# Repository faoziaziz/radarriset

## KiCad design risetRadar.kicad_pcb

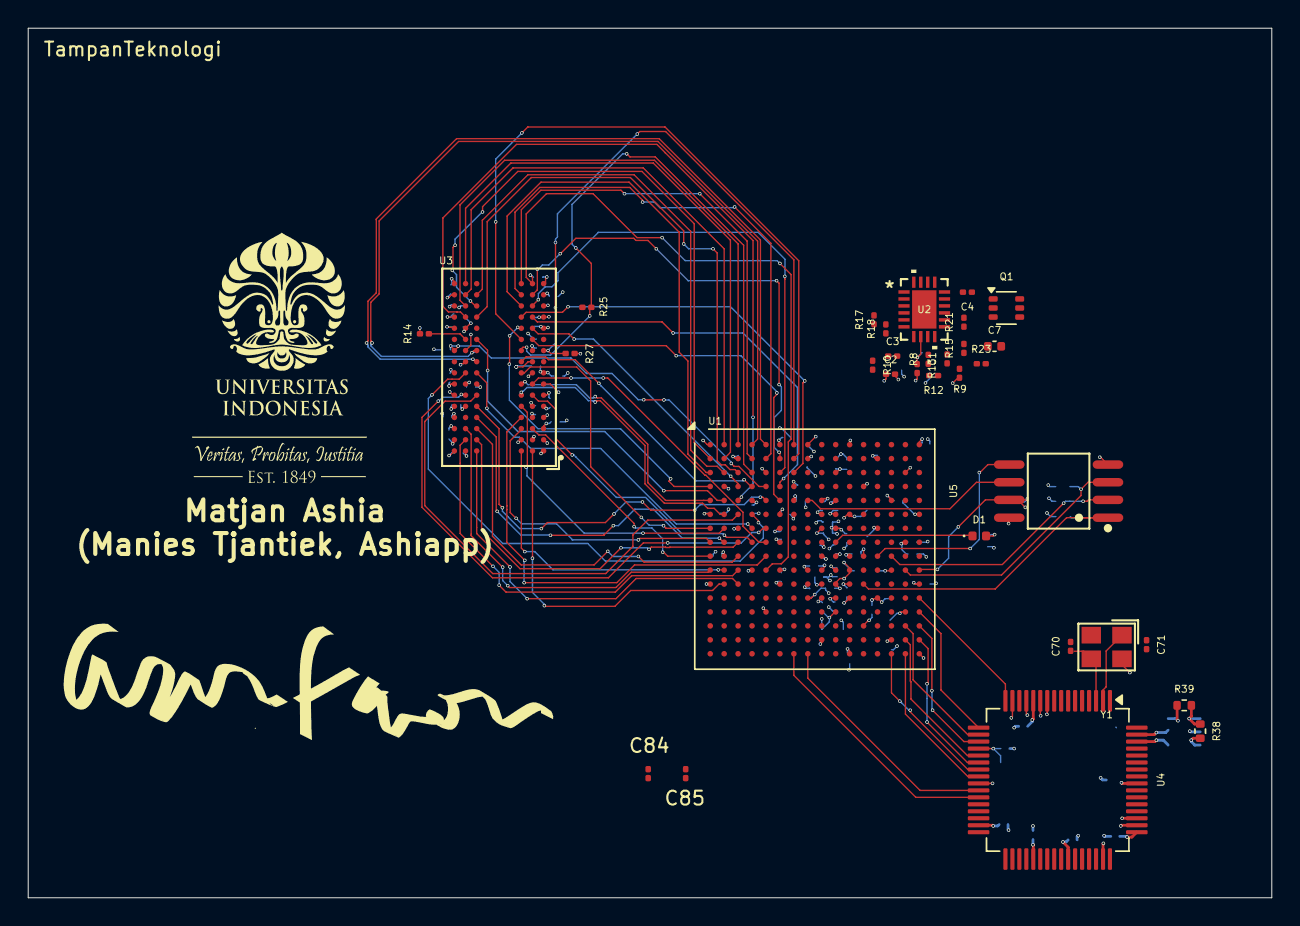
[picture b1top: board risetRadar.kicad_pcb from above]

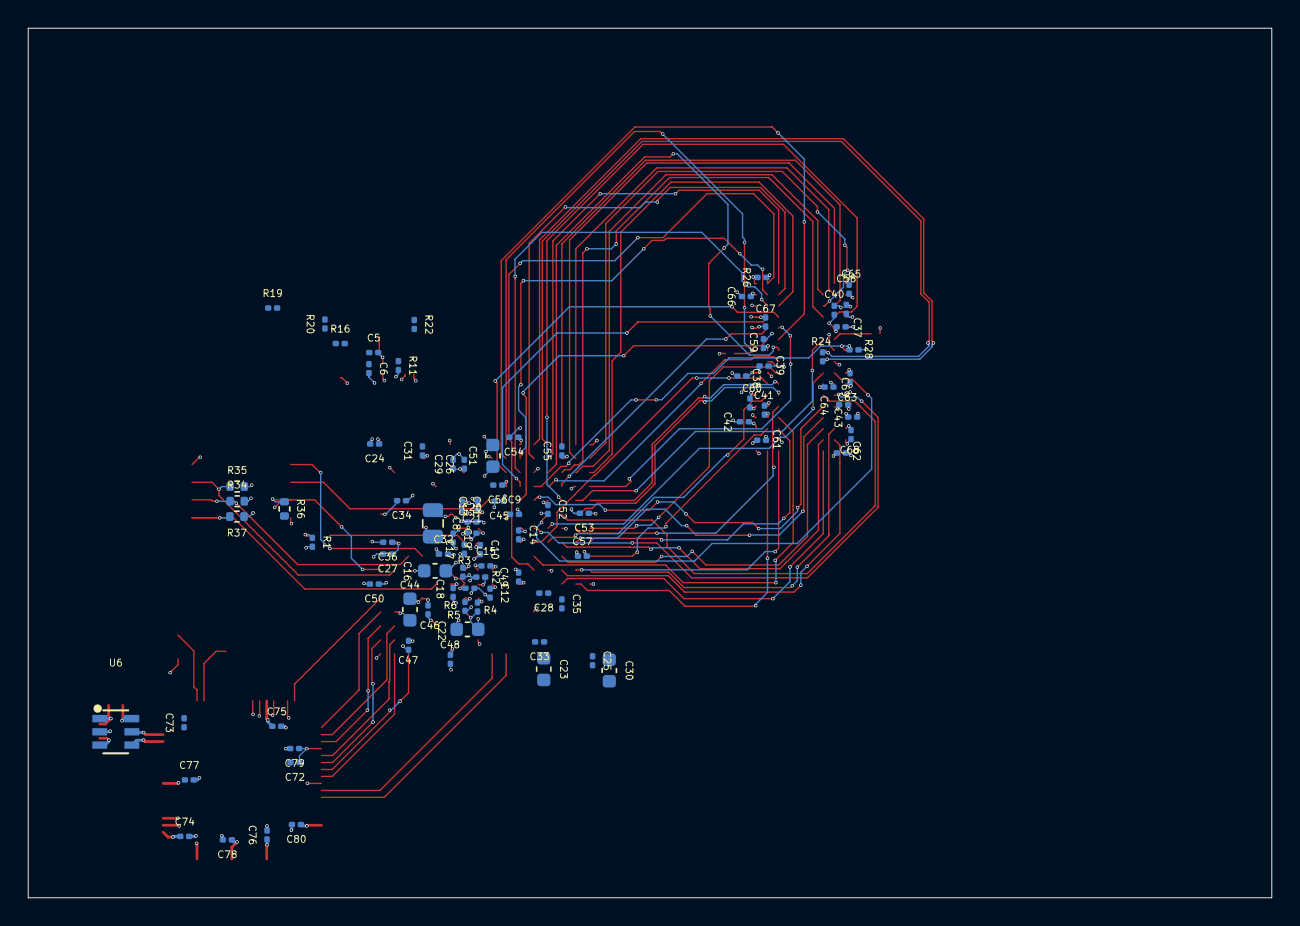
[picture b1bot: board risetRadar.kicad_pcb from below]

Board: 2 copper layers, 89.2 x 62.4 mm, 124 parts (92 on the bottom side), 96 nets.

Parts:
C1, C2, C3, C4, C5, C6: 20pF; C_0201_0603Metric
C7: 22uF; C_0402_1005Metric
C8: 100uF; C_0805_2012Metric
C9, C10, C14, C17, C18, C24, C25, C31, C32, C45, C46, C52, C53: 4.7uF; C_0201_0603Metric
C11, C12, C13, C15, C19, C20, C21, C26, C27, C28, C29, C33, C34, C35, C36, C47, C48, C49, C50, C54, C55, C56, C57, C84, C85: 0.47uF; C_0201_0603Metric
C16, C22, C23, C30, C44, C51: 47uF; C_0603_1608Metric
C37, C38, C39, C40, C41, C42, C43, C58, C59, C60, C61, C62, C63, C64, C65, C66, C67, C68, C69, C72, C73, C74, C75, C76, C77, C78, C79, C80: 0.1uF; C_0201_0603Metric
C70, C71: 8pF; C_0201_0603Metric
D1: LED; LED_0402_1005Metric
Q1: MBT3904DW1; SOT-363_SC-70-6
R1: 330R; R_0201_0603Metric
R2, R3, R26, R27, R28: 4.7K; R_0201_0603Metric
R4, R5, R6, R19: 1K; R_0201_0603Metric
R8, R10, R12: 180K; R_0201_0603Metric
R9, R11, R13: 57.6K; R_0201_0603Metric
R14: 240R; R_0201_0603Metric
R15: 3.48K; R_0201_0603Metric
R16: 10K; R_0201_0603Metric
R17, R20, R21, R22: 100K; R_0201_0603Metric
R18: 0; R_0201_0603Metric
R23: 680; R_0201_0603Metric
R24, R25: 100R; R_0201_0603Metric
R34, R37: 4.7K; R_0402_1005Metric
R35, R36: 1.8K; R_0402_1005Metric
R38: 2K; R_0402_1005Metric
R39: 10K; R_0402_1005Metric
U1: XC7A35T-FTG256; Xilinx_FTG256
U2: LTC3569EUDC; QFN-20_UDC_LIT
U3: MT41J128M16JT-125:KTR; FBGA-96_L14.0-W8.0-R16-C6-P0.80-TL
U4: FT2232HL; LQFP-64_10x10mm_P0.5mm
U5: MT25QL128ABA1ESE-MSITTR; SOP-8_L5.3-W5.3-P1.27-LS8.0-BL
U6: 93LC46BT-I/OT; SOT-23-6_L2.9-W1.6-P0.95-LS2.8-TL
Y1: Crystal_GND24; CRYSTAL-SMD_4P-L3.2-W2.5-BL

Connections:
/FPGA/FGPA_config/DONE: D1.1 (K), U1.H10 (DONE_0)
/FPGA/FGPA_config/INIT_B: R3.1, U1.K10 (INIT_B_0)
/FPGA/FGPA_config/M0: R4.1, U1.M9 (M0_0)
/FPGA/FGPA_config/M1: R5.1, U1.M10 (M1_0)
/FPGA/FGPA_config/M2: R6.1, U1.M11 (M2_0)
/FPGA/FGPA_config/PROG_B: R2.1, U1.L9 (PROGRAM_B_0)
/FPGA/FPGAIO1/FLASH_CS_N: R37.2, U1.L12 (IO_L6P_T0_FCS_B_14), U5.1 (S#)
/FPGA/FPGAIO1/FLASH_DQ0: U1.J13 (IO_L1P_T0_D00_MOSI_14), U5.5 (DQ0)
/FPGA/FPGAIO1/FLASH_DQ1: R34.1, U1.J14 (IO_L1N_T0_D01_DIN_14), U5.2 (DQ1)
/FPGA/FPGAIO1/FLASH_DQ2: R35.1, U1.K15 (IO_L2P_T0_D02_14), U5.3 (DQ2)
/FPGA/FPGAIO1/FLASH_DQ3: R36.1, U1.K16 (IO_L2N_T0_D03_14), U5.7 (DQ3)
/FPGA/FPGAIO2/DDR3_ADDR0: U1.C7 (IO_L5P_T0_AD13P_35), U3.N3 (A0)
/FPGA/FPGAIO2/DDR3_ADDR1: U1.B1 (IO_L9N_T1_DQS_AD7N_35), U3.P7 (A1)
/FPGA/FPGAIO2/DDR3_ADDR2: U1.C1 (IO_L9P_T1_DQS_AD7P_35), U3.P3 (A2)
/FPGA/FPGAIO2/DDR3_ADDR3: U1.D6 (IO_L6P_T0_35), U3.N2 (A3)
/FPGA/FPGAIO2/DDR3_ADDR4: U1.A3 (IO_L4N_T0_35), U3.P8 (A4)
/FPGA/FPGAIO2/DDR3_ADDR5: U1.C6 (IO_L5N_T0_AD13N_35), U3.P2 (A5)
/FPGA/FPGAIO2/DDR3_ADDR6: U1.A2 (IO_L8N_T1_AD14N_35), U3.R8 (A6)
/FPGA/FPGAIO2/DDR3_ADDR7: U1.B6 (IO_L2P_T0_AD12P_35), U3.R2 (A7)
/FPGA/FPGAIO2/DDR3_ADDR8: U1.B2 (IO_L8P_T1_AD14P_35), U3.T8 (A8)
/FPGA/FPGAIO2/DDR3_ADDR9: U1.B5 (IO_L2N_T0_AD12N_35), U3.R3 (A9)
/FPGA/FPGAIO2/DDR3_ADDR10: U1.E2 (IO_L10P_T1_AD15P_35), U3.L7 (A10/AP)
/FPGA/FPGAIO2/DDR3_ADDR11: U1.C2 (IO_L7N_T1_AD6N_35), U3.R7 (A11)
/FPGA/FPGAIO2/DDR3_ADDR12: U1.C3 (IO_L7P_T1_AD6P_35), U3.N7 (A12/BC#)
/FPGA/FPGAIO2/DDR3_ADDR13: U1.B4 (IO_L4P_T0_35), U3.T3 (A13)
/FPGA/FPGAIO2/DDR3_BA0: U1.D3 (IO_L11N_T1_SRCC_35), U3.M2 (BA0)
/FPGA/FPGAIO2/DDR3_BA1: U1.E3 (IO_L11P_T1_SRCC_35), U3.N8 (BA1)
/FPGA/FPGAIO2/DDR3_BA2: U1.D1 (IO_L10N_T1_AD15N_35), U3.M3 (BA2)
/FPGA/FPGAIO2/DDR3_CAS_N: R25.1, U1.C4 (IO_L12N_T1_MRCC_35), U3.K3 (CAS#)
/FPGA/FPGAIO2/DDR3_CKE: R28.1, U1.D5 (IO_L6N_T0_VREF_35), U3.K9 (CKE)
/FPGA/FPGAIO2/DDR3_CK_N: R24.2, U1.A4 (IO_L3N_T0_DQS_AD5N_35), U3.K7 (CK#)
/FPGA/FPGAIO2/DDR3_CK_P: R24.1, U1.A5 (IO_L3P_T0_DQS_AD5P_35), U3.J7 (CK)
/FPGA/FPGAIO2/DDR3_CS_N: U1.E6 (IO_0_35), U3.L2 (CS#)
/FPGA/FPGAIO2/DDR3_DM_0: U1.E5 (IO_L13N_T2_MRCC_35), U3.E7 (LDM)
/FPGA/FPGAIO2/DDR3_DM_1: U1.J5 (IO_L19P_T3_35), U3.D3 (UDM)
/FPGA/FPGAIO2/DDR3_DQ0: U1.G2 (IO_L17P_T2_35), U3.E3 (DQ0)
/FPGA/FPGAIO2/DDR3_DQ1: U1.F3 (IO_L14N_T2_SRCC_35), U3.F7 (DQ1)
/FPGA/FPGAIO2/DDR3_DQ2: U1.H4 (IO_L18N_T2_35), U3.F2 (DQ2)
/FPGA/FPGAIO2/DDR3_DQ3: U1.G5 (IO_L16P_T2_35), U3.F8 (DQ3)
/FPGA/FPGAIO2/DDR3_DQ4: U1.G1 (IO_L17N_T2_35), U3.H3 (DQ4)
/FPGA/FPGAIO2/DDR3_DQ5: U1.F4 (IO_L14P_T2_SRCC_35), U3.H8 (DQ5)
/FPGA/FPGAIO2/DDR3_DQ6: U1.H5 (IO_L18P_T2_35), U3.G2 (DQ6)
/FPGA/FPGAIO2/DDR3_DQ7: U1.G4 (IO_L16N_T2_35), U3.H7 (DQ7)
/FPGA/FPGAIO2/DDR3_DQ8: U1.H2 (IO_L20P_T3_35), U3.D7 (DQ8)
/FPGA/FPGAIO2/DDR3_DQ9: U1.H1 (IO_L20N_T3_35), U3.C3 (DQ9)
/FPGA/FPGAIO2/DDR3_DQ10: U1.K1 (IO_L22P_T3_35), U3.C8 (DQ10)
/FPGA/FPGAIO2/DDR3_DQ11: U1.J1 (IO_L22N_T3_35), U3.C2 (DQ11)
/FPGA/FPGAIO2/DDR3_DQ12: U1.L3 (IO_L23P_T3_35), U3.A7 (DQ12)
/FPGA/FPGAIO2/DDR3_DQ13: U1.L2 (IO_L23N_T3_35), U3.A2 (DQ13)
/FPGA/FPGAIO2/DDR3_DQ14: U1.K3 (IO_L24P_T3_35), U3.B8 (DQ14)
/FPGA/FPGAIO2/DDR3_DQ15: U1.K2 (IO_L24N_T3_35), U3.A3 (DQ15)
/FPGA/FPGAIO2/DDR3_DQS_0_N: U1.E1 (IO_L15N_T2_DQS_35), U3.G3 (LDQS#)
/FPGA/FPGAIO2/DDR3_DQS_0_P: U1.F2 (IO_L15P_T2_DQS_35), U3.F3 (LDQS)
/FPGA/FPGAIO2/DDR3_DQS_1_N: U1.H3 (IO_L21N_T3_DQS_35), U3.B7 (UDQS#)
/FPGA/FPGAIO2/DDR3_DQS_1_P: U1.J3 (IO_L21P_T3_DQS_35), U3.C7 (UDQS)
/FPGA/FPGAIO2/DDR3_ODT: R27.1, U1.A7 (IO_L1N_T0_AD4N_35), U3.K1 (ODT)
/FPGA/FPGAIO2/DDR3_RAS_N: U1.D4 (IO_L12P_T1_MRCC_35), U3.J3 (RAS#)
/FPGA/FPGAIO2/DDR3_RESET_N: R26.1, U1.K5 (IO_25_35), U3.T2 (RESET#)
/FPGA/FPGAIO2/DDR3_WE_N: U1.B7 (IO_L1P_T0_AD4P_35), U3.L3 (WE#)
FLASH_CLK: U1.E8 (CCLK_0), U5.6 (C)
FTDI_1V8: C73.1, C74.1, C75.1, C76.1, U4.12 (VCORE), U4.37 (VCORE), U4.49 (VREGOUT), U4.64 (VCORE)
FTDI_D0: U1.M16 (IO_L7P_T1_D09_14), U4.16 (ADBUS0)
FTDI_D1: U1.N16 (IO_L7N_T1_D10_14), U4.17 (ADBUS1)
FTDI_D2: U1.P15 (IO_L8P_T1_D11_14), U4.18 (ADBUS2)
FTDI_D3: U1.P16 (IO_L8N_T1_D12_14), U4.19 (ADBUS3)
FTDI_D4: U1.R15 (IO_L9P_T1_DQS_14), U4.21 (ADBUS4)
FTDI_D5: U1.R16 (IO_L9N_T1_DQS_D13_14), U4.22 (ADBUS5)
FTDI_D6: U1.T14 (IO_L10P_T1_D14_14), U4.23 (ADBUS6)
FTDI_D7: U1.T15 (IO_L10N_T1_D15_14), U4.24 (ADBUS7)
FTDI_RXE_N: U1.T8 (IO_L21N_T3_DQS_A06_D22_14), U4.26 (ACBUS0)
FTDI_TXE_N: U1.T7 (IO_L21P_T3_DQS_14), U4.27 (ACBUS1)
GNDREF: C2.2, C4.2, C6.2, C7.2, C8.2, C9.2, C10.2, C11.2, C12.2, C13.2, C14.2, C15.2, C16.2, C17.2, C18.2, C19.2, C20.2, C21.2, C22.2, C23.2, C24.2, C25.2, C26.2, C27.2, C28.2, C29.2, C30.2, C31.2, C32.2, C33.2, C34.2, C35.2, C36.2, C37.2, C38.2, C39.2, C40.2, C41.2, C42.2, C43.2, C44.2, C45.2, C46.2, C47.2, C48.2, C49.2, C50.2, C51.2, C52.2, C53.2, C54.2, C55.2, C56.2, C57.2, C58.2, C59.2, C60.2, C61.2, C62.2, C63.2, C64.2, C65.2, C66.2, C67.2, C68.2, C69.2, C70.2, C71.2, C72.2, C73.2, C74.2, C75.2, C76.2, C77.2, C78.2, C79.2, C80.2, C84.2, C85.2, Q1.1 (E1), Q1.4 (E2), R5.2, R6.2, R9.2, R11.2, R13.2, R14.2, R16.2, R17.2, R25.2, R26.2, R27.2, R28.2, U1.A1 (GND), U1.A11 (GND), U1.B8 (GND), U1.C5 (GND), U1.C15 (GND), U1.D2 (GND), U1.D12 (GND), U1.E9 (GND), U1.F6 (GND), U1.F10 (GND), U1.F16 (GND), U1.G3 (GND), U1.G9 (GND), U1.G13 (GND), U1.H6 (GND), U1.J9 (GND), U1.J11 (GND), U1.K4 (GND), U1.K6 (GND), U1.K7 (DXN_0), U1.K8 (DXP_0), U1.K14 (GND), U1.L1 (GND), U1.L11 (GND), U1.M8 (GND), U1.N5 (GND), U1.N15 (GND), U1.P2 (GND), U1.P12 (GND), U1.R9 (GND), U1.T6 (GND), U1.T16 (GND), U2.1 (PGND2), U2.11 (SGND), U2.15 (PGND3), U2.20 (PGND1), U2.21 (GND), U3.A9 (VSS), U3.B1 (VSSQ), U3.B3 (VSS), U3.B9 (VSSQ), U3.D1 (VSSQ), U3.E1 (VSS), U3.E2 (VSSQ), U3.E8 (VSSQ), U3.F9 (VSSQ), U3.G1 (VSSQ), U3.G8 (VSS), U3.G9 (VSSQ), U3.J2 (VSS), U3.J8 (VSS), U3.M1 (VSS), U3.M9 (VSS), U3.P1 (VSS), U3.P9 (VSS), U3.T1 (VSS), U3.T9 (VSS), U4.1 (GND), U4.5 (GND), U4.10 (AGND), U4.11 (GND), U4.13 (TEST), U4.15 (GND), U4.25 (GND), U4.35 (GND), U4.47 (GND), U4.51 (GND), U5.4 (VSS), U6.2 (VSS), Y1.2, Y1.4
unnamed: D1.2 (A), R1.1
unnamed: Q1.2 (B1), Q1.3 (C2), R20.2
unnamed: Q1.6 (C1), R21.2, U2.13 (EN2)
unnamed: Q1.5 (B2), R19.2
unnamed: R15.2, R16.1, U2.12 (EN3)
unnamed: C5.2, R12.2, R13.1, U2.8 (FB1)
unnamed: C3.2, R10.2, R11.1, U2.7 (FB2)
unnamed: C1.2, R8.2, R9.1, U2.9 (FB3)
unnamed: R17.1, R18.2, U2.5 (MODE)
unnamed: R14.1, U3.L8 (ZQ)
unnamed: U4.62 (EECLK), U6.4 (CLK)
unnamed: U4.63 (EECS), U6.5 (CS)
unnamed: C71.1, U4.2 (OSCI), Y1.1
unnamed: C70.1, U4.3 (OSCO), Y1.3
unnamed: R38.2, U6.3 (DI)
unnamed: R38.1, R39.2, U6.1 (DO)
PGOOD: R22.2, U2.4 (PGOOD)
VCC1V0: C5.1, C6.1, C8.1, C9.1, C10.1, C11.1, C12.1, C13.1, C14.1, C15.1, R12.1, R19.1, U1.E10 (VCCBRAM), U1.F7 (VCCINT), U1.F9 (VCCINT), U1.F11 (VCCBRAM), U1.G6 (VCCINT), U1.H9 (VCCINT), U1.J6 (VCCINT), U1.K9 (VCCINT), U1.L8 (VCCINT)
VCC1V5: C41.1, C42.1, C43.1, C51.1, C52.1, C53.1, C54.1, C55.1, C56.1, C57.1, C58.1, C59.1, C60.1, C61.1, C62.1, C63.1, C64.1, C65.1, C66.1, C67.1, C68.1, C69.1, U1.A6 (VCCO_35), U1.B3 (VCCO_35), U1.D7 (VCCO_35), U1.E4 (VCCO_35), U1.F1 (VCCO_35), U1.J2 (VCCO_35), U3.A1 (VDDQ), U3.A8 (VDDQ), U3.B2 (VDD), U3.C1 (VDDQ), U3.C9 (VDDQ), U3.D2 (VDDQ), U3.D9 (VDD), U3.E9 (VDDQ), U3.F1 (VDDQ), U3.G7 (VDD), U3.H2 (VDDQ), U3.H9 (VDDQ), U3.K2 (VDD), U3.K8 (VDD), U3.N1 (VDD), U3.N9 (VDD), U3.R1 (VDD), U3.R9 (VDD)
VCC1V8: C3.1, C4.1, C16.1, C17.1, C18.1, C19.1, C20.1, C21.1, C85.1, R10.1, R15.1, U1.G10 (VCCAUX), U1.J10 (VCCAUX), U1.K11 (VCCAUX), U1.L10 (VCCAUX)
VCC3V3: C1.1, C2.1, C22.1, C44.1, C45.1, C46.1, C47.1, C48.1, C49.1, C50.1, C72.1, C77.1, C78.1, C79.1, C80.1, R1.2, R2.2, R3.2, R4.2, R8.1, R22.1, R23.1, R34.2, R35.2, R36.2, R37.1, R39.1, U1.E7 (CFGBVS_0), U1.L6 (VCCO_0), U1.L16 (VCCO_14), U1.M13 (VCCO_14), U1.N10 (VCCO_14), U1.P7 (VCCO_14), U1.R14 (VCCO_14), U1.T11 (VCCO_14), U4.20 (VCCIO), U4.31 (VCCIO), U4.42 (VCCIO), U4.50 (VREGIN), U4.56 (VCCIO), U5.8 (VCC), U6.6 (VCC)
VCCIO: C23.1, C24.1, C25.1, C26.1, C27.1, C28.1, C29.1, C30.1, C31.1, C32.1, C33.1, C34.1, C35.1, C36.1, U1.A16 (VCCO_15), U1.B13 (VCCO_15), U1.C10 (VCCO_15), U1.E14 (VCCO_15), U1.H15 (VCCO_15), U1.J12 (VCCO_15), U1.M3 (VCCO_34), U1.R4 (VCCO_34), U1.T1 (VCCO_34)
VTTVREF: C37.1, C38.1, C39.1, C40.1, U3.H1 (VREFDQ), U3.M8 (VREFCA)
VU: C7.1, R18.1, R20.1, R21.1, U2.3 (PVIN), U2.6 (RT), U2.10 (SVIN), U2.14 (EN1), U2.17 (PVIN3), U2.18 (PVIN1)

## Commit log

2025-11-02 add riset radar
2025-11-03 add
    add
